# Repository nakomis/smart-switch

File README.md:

# Petro: a 10 A mains Wi-Fi smart switch

## Support

If you find this useful, please consider buying me a coffee:

## Table of Contents

<!-- toc -->

- [What it is](#what-it-is)
- [⚠️ Safety](#%E2%9A%A0%EF%B8%8F-safety)
- [Architecture Diagram](#architecture-diagram)
- [Repository Layout](#repository-layout)
- [Status](#status)
- [Architecture Diagrams](#architecture-diagrams)
- [Licence](#licence)
- [Support](#support)

<!-- tocstop -->

## What it is

Petro is a home-built Wi-Fi smart switch: an in-line cord unit (cable in, cable out) that switches a
resistive load of up to **10 A at 230 V AC**. It has:

- energy metering (voltage, current, power and energy totals), from a BL0939;
- one tactile button that cycles **on → off → auto**;
- a multi-colour status LED for the mode, boot, Wi-Fi, pairing and faults;
- control over MQTT through AWS IoT Core, using Martin's Fleet device service, with OTA
  updates and rollback;
- Alexa Smart Home control;
- back-up over-current and over-temperature trips in firmware.

It runs on an ESP32-C6, powered straight from the mains by a non-isolated buck converter, so the
whole board is at mains potential: it is only ever powered closed in its case, and USB is used
only with mains unplugged.

Petro is named after a Clone Wars youngling: microcontrollers in this house are Younglings.

## ⚠️ Safety

**This is a mains device, built for its author's own home. It is not a product, it will never be
sold or given away, and it has not been safety tested or UKCA marked.** The designs are published
for interest. If you build one, you do so at your own risk: mains electricity can kill, and a badly
built 10 A switch can start a fire.

## Architecture Diagram

The board's block diagram and the system diagram are still to come
(`docs/architecture/smart-switch.drawio`).

## Repository Layout

| Path | What's there |
|---|---|
| `pcb/` | The board, generated as code: a Python generator for KiCad 10, with DRC rules for mains creepage and 10 A tracks, and outputs for PCBWay and JLCPCB |
| `firmware/` | ESP-IDF 5.5 firmware for the ESP32-C6: portable C with host tests, plus the IDF project |
| `case/` | The enclosure: a printed case in UL94 V-0 flame-retardant filament, with glands and cord grips |
| `infra/` | AWS, as CDK in TypeScript: the units' IoT Things, CI's role, and the Alexa skill's Lambda, account linking and state |
| `alexa/` | The Alexa Smart Home skill as code: its manifest and icons (`docs/alexa-setup.md`) |
| `docs/` | Design notes, the test procedures for the safety gates, the Alexa setup, the logo |
| `.github/workflows/` | CI |

## Status

The board (PETRO-2) is designed and routed: revision B, 120 × 80 mm with 4 mm rounded corners, two layers, generated as code
in `pcb/` and DRC-clean against its own mains rules. It passed its design review (safety gate 1) and five
were ordered on 5 Nov 2026. The firmware (PETRO-3 to PETRO-5) and the case (PETRO-6) are next.
The safety gates' procedures and results are in [`docs/testing/`](docs/testing/README.md).
The design decisions, and why, are in [`docs/DESIGN.md`](docs/DESIGN.md).

## Architecture Diagrams

`docs/architecture/smart-switch.drawio` will be the source for the diagram above. The SVG is
auto-regenerated on commit by the pre-commit hook in `.githooks/pre-commit`.

To activate the hook after cloning:

```bash
git config core.hooksPath .githooks
```

## Licence

[CC0 1.0 Universal](LICENSE).

## Support

If you find this useful, please consider buying me a coffee:

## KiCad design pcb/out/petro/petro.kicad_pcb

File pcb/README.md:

# Board

The Petro board, generated as code (Python → KiCad 10) on the nakostat heatlink pipeline
(`nakostat/pcb/heatlink/`, itself from tinycrypt's), with DRC rules for mains creepage and a
`Mains16A` net class. Work item: PETRO-2, after the design decisions in PETRO-1.

The pipeline is copied, not shared: `board/` holds the generic modules, and Petro's own board
arrives as `board/petro_board.py` and `build.py`.

| Module | What it does |
|---|---|
| `board/sexpr.py` | Reads and writes KiCad s-expressions |
| `board/kicadlib.py` | Loads footprints (pads, courtyards) and symbol pin tables |
| `board/parts.py` | The parts catalogue: LCSC number, footprint, symbol, body extent, 3D model fixes, manufacturer |
| `board/netlist.py` | `Circuit` (parts and nets) and `check()` (single-pad nets, nets with several outputs, unconnected power pins) |
| `board/placement.py` | `Placement` and rotated bounding boxes |
| `board/kicad_pcb.py` | Writes `.kicad_pcb`, `.kicad_pro` (net classes) and `.kicad_dru` (mains rules) |
| `board/dsn.py`, `board/ses.py`, `board/route.py` | Specctra DSN out, Freerouting headless, SES back in |
| `board/cleanup.py` | After routing, drops vias that join only one layer and track stubs that lead nowhere |
| `board/fab.py` | BOMs (JLCPCB and PCBWay), CPL, gerbers, drill, renders, STEP |
| `board/art.py` | Turns a black-and-white PNG into a silkscreen portrait |
| `board/rules.py` | The mains rules: potential groups, fault scenarios, the working-voltage matrix, IEC 60664-1 creepage, the generated `.kicad_dru` and net classes, and the creepage check within barrier parts |

## Mains rules

Every mains net is in one potential group:

| Group | What's in it |
|---|---|
| LINE | Live before F1 |
| LIVE | Live after F1 |
| PSU | Live after F2: the supply's DC bus |
| SWNODE | The LNK306's switching node and what rides on it (SW, BP, FB, FBH) |
| NEUTRAL | Neutral, and every other net: GND is neutral |
| LOAD | The relay's output |
| DIV1–4 | The voltage divider's chain |

Rev B is non-isolated (`Rules(rest="NEUTRAL")`): every net not named in a group sits at neutral,
so the low-voltage side is one more mains potential. Each fault scenario (relay closed or open,
either fuse blown) gives every group a potential. The worst difference between two groups is
their working voltage, and IEC 60664-1 Table F.4 (pollution degree 2, material group III) turns
that into a creepage distance: 2.5 mm between the mains potentials, less down the divider's chain,
and 1.0 mm for SWNODE (`Rules.reduced`: functional insulation inside the converter). `rules.py`
writes the result as KiCad DRC rules, and `tests/test_rules.py` proves each rule fails a board
that breaks it.

`rules.py` still supports the isolated designs (rev A's 8 mm mains↔SELV barrier, and rev B's
isolated J3 as a SELV island, with `barrier_creepage()` for the pads of certified barrier parts),
but Petro's board uses neither now: see the tags in `docs/DESIGN.md`.

The high-current nets (N_IN, N_OUT, L_IN, L_F, L_OUT) are not tracks but solid pours on both
layers, stitched with vias (`petro_board.mains_zones()` and `stitch_vias()`). Each pour is drawn
as a generous polygon, and KiCad's fill trims it to the rules. Its `min_thickness` is the
IPC-2221 width for 8 A at 1 oz (3.5 mm), half the 16 A design current, so KiCad drops any neck
thinner than that. `tests/test_copper.py` refills the zones and checks that each layer, on its
own, is one piece reaching every through-hole pad of its net, so the two layers carry the current
in parallel. The GND pour covers the low-voltage area, kept 2.5 mm from every other potential.

## Routing

`build.py --route` routes in one Freerouting pass: the low-voltage nets inside the low-voltage
area (`petro_board.lv_area()`), with keep-outs round everything at another potential, since the
router knows only plain clearances. By hand, before routing (`petro_board.hand_wiring()`): the
divider chain, the supply's high-voltage nets, the shunt's Kelvin pair (into R10), the LDO's
ground and the USB protection's flow-through ties. DRC then runs with the generated rules, and
the build fails on any error, unconnected item or broken mains pour.

## Setting up

```bash
cd pcb
ASDF_PYTHON_VERSION=3.11.15 python3 -m venv .venv
.venv/bin/pip install -r requirements.txt
cp ~/repos/nakomis/nakostat/pcb/heatlink/freerouting/freerouting-2.5.0.jar freerouting/   # 64 MB, not committed
```

Java comes from asdf. KiCad 10 must be installed at `/Applications/KiCad/`.

- `./fetch_parts.sh` fetches any missing footprints and symbols from EasyEDA. It skips parts it
  already has, and waits 20 s between parts because EasyEDA rate-limits.
- `./fetch_models.sh` fetches the 3D models, which aren't committed.

## Tests

```bash
TEST_MAX_WORKERS=2 .venv/bin/python -m pytest -q tests
```

Tests marked `kicad` run `kicad-cli` (DRC, position files) or read KiCad's footprint library.
Without KiCad they're skipped, not failed, and the rest still run: that's how CI runs them (PETRO-9),
so the DRC-backed tests still need a run on the Mac before a board is ordered. `KICAD_CLI` and
`KICAD_FP` override the macOS paths.

The generic tests run on a small fixture board (`tests/fixture_board.py`), not on Petro's board.
The routing test routes that fixture with Freerouting **in a temporary directory**. Freerouting
isn't deterministic, so a test that routed in place would overwrite `out/` (the heatlink nearly
committed a re-routed board after its order had been quoted). The board that gets ordered is
committed and tagged.

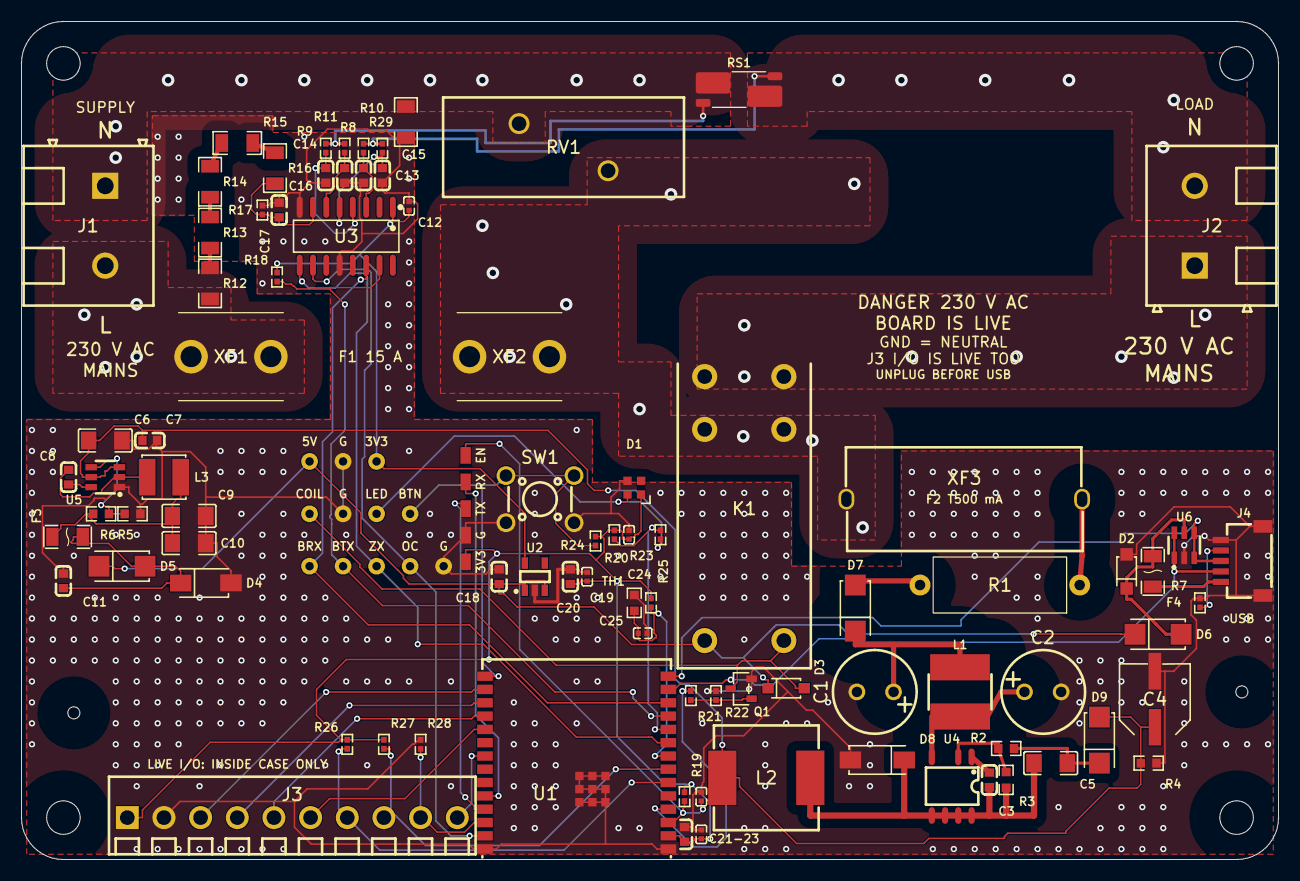
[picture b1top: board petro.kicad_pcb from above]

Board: 2 copper layers, 120.0 x 80.0 mm, 106 parts (0 on the bottom side), 60 nets.

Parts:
C1, C2: 4.7uF 400V; CAP-TH_BD8.0-P3.50-D0.6-FD
C3, C7, C8: 100nF; C0603
C4: 220uF 25V; CAP-SMD_BD6.3-L6.6-W6.6-LS7.2-FD
C5, C6: 10uF 50V; C1206
C9, C10: 22uF 25V; C1206
C11, C18, C19, C21: 10uF; C0603
C12, C20, C22, C24, C25: 100nF; C0402
C13, C14, C15, C16, C17: 33nF; C0603
C23: 1uF; C0402
D1: SK6812-EC20; LED-SMD_4P-L2.0-W2.0-BR
D2: SMF5.0A; SOD-123FL_L2.7-W1.8-LS3.8-RD
D3: 1N4148W; SOD-123F_L2.7-W1.6-LS3.8-RD
D4: SMAJ5.0A; SMA_L4.3-W2.6-LS5.0-RD
D5, D6: SS34; SMA_L4.3-W2.6-LS5.2-RD
D7, D9: M7; SMA_L4.3-W2.6-LS5.2-RD
D8: US1M; SMA_L4.4-W2.8-LS5.4-RD
F3: 1.1A PTC; F1206
F4: 500mA PTC; F1206
H1, H2, H3, H4: M3 hole, unplated; MountingHole_M3_3.2mm_NPTH
H5, H6: tooling hole; ToolingHole_1.152mm_NPTH
J1, J2: DG636-7.62-02P; CONN-TH_DG636-7.62-02P-14-02A-H
J3: DB125-3.5-10P-GN-S; CONN-TH_10P-P3.50_DIBO_DB125-3.5-10P-GN-S
J4: SM05B-SRSS-G-TB; CONN-SMD_SM05B-SRSS-G-TB-LF-SN
K1: HF115F-I/005-1HS3A; RELAY-TH_HF115F-XXX-1HS3
L1: 1mH 350mA; IND-SMD_L6.0-W6.0_FNR60XXS
L2: 680uH 1A; IND-SMD_L10.0-W10.0_ABG10A50M4R7
L3: 3.3uH; IND-SMD_L4.0-W4.0
Q1: AO3400A; SOT-23-3_L2.9-W1.3-P1.90-LS2.4-BR
R1: 10R 2W fusible; R_Axial_FKN2WS_P15.24mm
R2: 13k; R0603
R3: 2k; R0603
R4: 3k3; R0603
R5: 56k; R0603
R6: 10k; R0603
R7: 5k1; R0402
R8, R9, R10, R11: 1k; R0402
R12, R13, R14, R15, R16: 390k; R1206
R17: 470R; R0402
R18, R19, R20, R24, R25: 10k; R0402
R21: 100R; R0402
R22, R28: 100k; R0402
R23: 330R; R0402
R26, R27: 4k7; R0402
R29: 0R; R1206
RS1: 1mR; R_Shunt_Vishay_WSK2512_6332Metric_T2.21mm
RV1: TMOV20RP275E; RES-TH_L23.0-W9.5-P8.50-D0.9-S4.50
SW1: TS-1002 7mm; SW-TH_4P-L6.0-W6.0-P4.50-LS6.5_TS-1002-07026
TH1: 10k NTC; R0603
TP1: Debug pads; DebugPads_1x5_P2.54
TP2, TP3, TP4, TP5, TP6, TP7, TP8, TP9, TP10, TP11, TP12, TP13: test hole; TestHole_0.8mm
U1: ESP32-C6-WROOM-1-N8; ESP32-C6-WROOM-1_NoThermalVias
U2: AP2112K-3.3TRG1; SOT-25-5_L2.9-W1.6-P0.95-LS2.8-BL
U3: BL0939; SOP-16_L9.9-W3.9-P1.27-LS6.0-BL
U4: LNK306DN; SOIC-8_7P-L4.9-W3.9-P1.27-LS6.0-BL-PE3
U5: TPS563201; SOT-23-6_L2.9-W1.6-P0.95-LS2.8-BR
U6: SRV05-4; SOT-23-6_L2.9-W1.6-P0.95-LS2.8-BL-1
XF1, XF2: 6.35mm fuse clip 30A; FuseClip_Littelfuse_0122_6.35mm
XF3: 5x20 holder; FUSE-TH_65600001009

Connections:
+3V3: C12.1, C19.1, C20.1, C21.1, C22.1, C24.1, D1.1, J3.1, R18.2, R19.2, R20.2, R24.2, R25.2, R26.2, R27.2, TP1.5, TP9.1, U1.2, U2.5, U3.1
+5V: C18.1, D3.1, D5.1, D6.1, K1.1, TP7.1, U2.1, U2.3
+12V: C4.1, C6.1, C7.1, D9.2, L2.2, R4.1, U5.3, U5.5
BL_RX: TP2.1, U1.12, U3.14
BL_TX: R18.1, TP3.1, U1.11, U3.15
BP: C3.1, U4.1
BST5: C8.1, U5.6
BUTTON: R20.1, SW1.1, SW1.2, TP13.1, U1.15
CC: J4.4, R7.1
COIL: D3.2, K1.2, Q1.3, TP10.1
DIV1: R15.2, R16.1
DIV2: R14.2, R15.1
DIV3: R13.2, R14.1
DIV4: R12.2, R13.1
EN: C23.1, R19.1, TP1.1, U1.3
FB: R2.2, R3.1, U4.2
FB5: R5.2, R6.1, U5.4
FBH: C5.1, D9.1, R2.1
GND: C1.2, C2.2, C4.2, C6.2, C7.2, C9.2, C10.2, C11.2, C12.2, C13.2, C14.2, C15.2, C16.2, C17.2, C18.2, C19.2, C20.2, C21.2, C22.2, C23.2, C24.2, C25.2, D1.3, D2.2, D4.2, D8.2, J3.2, J4.5, J4.6, J4.7, Q1.2, R4.2, R6.2, R7.2, R17.2, R22.2, R28.2, R29.1, SW1.3, SW1.4, TH1.2, TP1.4, TP6.1, TP8.1, TP11.1, U1.1, U1.28, U1.29, U1.30, U1.31, U1.32, U1.33, U1.34, U1.35, U1.36, U1.37, U2.2, U3.8, U3.12, U5.1, U6.2
I2C_SCL: J3.8, R27.1, U1.7
I2C_SDA: J3.7, R26.1, U1.6
IAN: C14.1, R9.2, U3.4
IAP: C13.1, R8.2, U3.3
IBN: C16.1, R11.2, U3.6
IBP: C15.1, R10.2, U3.5
IO_IN: J3.9, R28.1, U1.26
IO_OUT: J3.10, U1.21
KGND: R9.1, R11.1, RS1.2
LED: R23.2, R24.1, U1.10
LED_DIN: D1.4, R23.1, TP12.1
L_F: K1.5, K1.6, RV1.1, XF2.1, XF3.1
L_IN: J1.2, R12.1, XF1.1
L_OUT: J2.1, K1.7, K1.8
L_PSU: R1.1, XF3.2
L_RF: D7.2, R1.2
NTC: C25.1, R25.1, TH1.1, U1.8
N_IN: J1.1, R29.2, RS1.1, RV1.2
N_OUT: J2.2, RS1.4
OC: TP5.1, U1.27, U3.10
RELAY: R21.2, U1.4
RELAY_G: Q1.1, R21.1, R22.1
SENSE: R8.1, R10.1, RS1.3
SPI_CS: J3.6, U1.19
SPI_MISO: J3.5, U1.18
SPI_MOSI: J3.4, U1.17
SPI_SCLK: J3.3, U1.16
SW: C3.2, C5.2, D8.1, L2.1, R3.2, U4.5, U4.6, U4.7, U4.8
SW5: C8.2, L3.1, U5.2
UART_RX: TP1.2, U1.24
UART_TX: TP1.3, U1.25
USB_DM: J4.2, U1.13, U6.1, U6.6
USB_DP: J4.3, U1.14, U6.3, U6.4
VBULK: C2.1, L1.2, U4.4
VBULK1: C1.1, D7.1, L1.1
VBUS: D2.1, D6.2, F4.2, U6.5
VBUS_IN: F4.1, J4.1
VP: C17.1, R16.2, R17.1, U3.7
VPSU: C9.1, C10.1, F3.1, L3.2, R5.1
VPSU_F: C11.1, D4.1, D5.2, F3.2
ZX: TP4.1, U1.9, U3.9

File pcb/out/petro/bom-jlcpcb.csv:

Comment,Designator,Footprint,LCSC Part #
4.7uF 400V,"C1,C2",CAP-TH_BD8.0-P3.50-D0.6-FD,C112482
100nF,"C3,C7,C8",C0603,C14663
220uF 25V,C4,CAP-SMD_BD6.3-L6.6-W6.6-LS7.2-FD,C4747974
10uF 50V,"C5,C6",C1206,C13585
22uF 25V,"C9,C10",C1206,C12891
10uF,"C11,C18,C19,C21",C0603,C19702
100nF,"C12,C20,C22,C24,C25",C0402,C1525
33nF,"C13,C14,C15,C16,C17",C0603,C21117
1uF,C23,C0402,C52923
SK6812-EC20,D1,LED-SMD_4P-L2.0-W2.0-BR,C2909058
SMF5.0A,D2,SOD-123FL_L2.7-W1.8-LS3.8-RD,C19077497
1N4148W,D3,SOD-123F_L2.7-W1.6-LS3.8-RD,C81598
SMAJ5.0A,D4,SMA_L4.3-W2.6-LS5.0-RD,C2925443
SS34,"D5,D6",SMA_L4.3-W2.6-LS5.2-RD,C8678
M7,"D7,D9",SMA_L4.3-W2.6-LS5.2-RD,C95872
US1M,D8,SMA_L4.4-W2.8-LS5.4-RD,C412437
1.1A PTC,F3,F1206,C126818
500mA PTC,F4,F1206,C163512
DB125-3.5-10P-GN-S,J3,CONN-TH_10P-P3.50_DIBO_DB125-3.5-10P-GN-S,C5184956
SM05B-SRSS-G-TB,J4,CONN-SMD_SM05B-SRSS-G-TB-LF-SN,C265419
1mH 350mA,L1,IND-SMD_L6.0-W6.0_FNR60XXS,C168102
680uH 1A,L2,IND-SMD_L10.0-W10.0_ABG10A50M4R7,C48934988
3.3uH,L3,IND-SMD_L4.0-W4.0,C602030
AO3400A,Q1,SOT-23-3_L2.9-W1.3-P1.90-LS2.4-BR,C20917
13k,R2,R0603,C22797
2k,R3,R0603,C22975
3k3,R4,R0603,C22978
56k,R5,R0603,C23206
10k,R6,R0603,C25804
5k1,R7,R0402,C25905
1k,"R8,R9,R10,R11",R0402,C11702
390k,"R12,R13,R14,R15,R16",R1206,C17933
470R,R17,R0402,C25117
10k,"R18,R19,R20,R24,R25",R0402,C25744
100R,R21,R0402,C25076
100k,"R22,R28",R0402,C25741
330R,R23,R0402,C25104
4k7,"R26,R27",R0402,C25900
0R,R29,R1206,C17888
1mR,RS1,R_Shunt_Vishay_WSK2512_6332Metric_T2.21mm,C4248455
TS-1002 7mm,SW1,SW-TH_4P-L6.0-W6.0-P4.50-LS6.5_TS-1002-07026,C455095
10k NTC,TH1,R0603,C2892547
ESP32-C6-WROOM-1-N8,U1,ESP32-C6-WROOM-1_NoThermalVias,C5366877
AP2112K-3.3TRG1,U2,SOT-25-5_L2.9-W1.6-P0.95-LS2.8-BL,C51118
BL0939,U3,SOP-16_L9.9-W3.9-P1.27-LS6.0-BL,C2836697
LNK306DN,U4,SOIC-8_7P-L4.9-W3.9-P1.27-LS6.0-BL-PE3,C34318
TPS563201,U5,SOT-23-6_L2.9-W1.6-P0.95-LS2.8-BR,C116592
SRV05-4,U6,SOT-23-6_L2.9-W1.6-P0.95-LS2.8-BL-1,C7420376

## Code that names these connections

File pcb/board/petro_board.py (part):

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# sensors and the PIR can wake the chip with the main core asleep; SPI on 18-21. IN (3), OUT (23)
# and SPI are on the module's left-hand column, J3's side; LP_I2C has no other pins. GPIO22 and
# GPIO15 are spare.
GPIO = {"BUTTON": 9, "LED": 8, "USB_DM": 12, "USB_DP": 13, "UART_TX": 16, "UART_RX": 17,
        "NTC": 0,           # board temperature, ADC1_CH0
        "ZX": 1,            # BL0939 zero cross
        "OC": 2,            # BL0939 I_leak (channel B fast over-current)
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# --- connectors ----------------------------------------------------------------------------------
# J1 / J2: line in and load out (Degson DG636, 7.62 mm). Earth does not touch the board. Both
# turned so their wire openings face their end of the board (J1 left, J2 right), neutral on top.
J1_PINS = {"1": "N_IN", "2": "L_IN"}           # rotated 270: pad 1 on top
J2_PINS = {"1": "L_OUT", "2": "N_OUT"}         # rotated 90: pad 2 on top
# J4: the house USB connector (tinycrypt's J1, as on the heatlink): 1 VBUS, 2 D-, 3 D+, 4 CC,
# 5 GND; pads 6/7 are the shell tabs. Inside the case: reachable only with the case off.
USB_PINS = {"1": "VBUS_IN", "2": "USB_DM", "3": "USB_DP", "4": "CC", "5": "GND"}
DEBUG_PINS = {"1": "EN", "2": "UART_RX", "3": "UART_TX", "4": "GND", "5": "+3V3"}
# J3: the I/O terminal (10-way, 3.5 mm) for parts inside the case, straight from the ESP32: 3.3 V
# and ground, SPI, I2C, one input (a PIR, an interrupt) and one output. At mains potential, like
# the rest of the board. J4 (the heatlink's IDC header) is gone: the C6 has no pins left for it.
IO_PINS = {"1": "+3V3", "2": "GND", "3": "SPI_SCLK", "4": "SPI_MOSI", "5": "SPI_MISO",
           "6": "SPI_CS", "7": "I2C_SDA", "8": "I2C_SCL", "9": "IO_IN", "10": "IO_OUT"}

# --- the mains rules (non-isolated mode: every other net sits at neutral) --------------------------
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    # ---- the supply: F2, then PI's LNK306 high-side buck (12 V) ----------------------------------
    two("FUSEHOLD", "XF3", "L_F", "L_PSU")                      # F2, T500 mA
    two("RFUSE", None, "L_PSU", "L_RF")                         # fusible, flameproof: inrush and fault
    pins("RECT", "D7", A="L_RF", K="VBULK1")                          # half-wave, in the live leg
    pins("C4U7HV", _plus="VBULK1", _minus=gnd)                  # pi filter: C4, L2, C5
    two("L1MF", None, "VBULK1", "VBULK")
    pins("C4U7HV", _plus="VBULK", _minus=gnd)
    u4 = part("LNK306", "U4")
    c.connect("VBULK", (u4, "D"))
    c.connect("SW", (u4, "S"))
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    two("L680U", None, "SW", v12)                               # output inductor, 680 uH (>= 0.5 mH, PI MDCM)
    pins("FASTREC", "D8", A=gnd, K="SW")                              # freewheel (US1M, 75 ns)
    pins("C220U", _plus=v12, _minus=gnd)
    pins("RECT", "D9", A=v12, K="FBH")                                # feedback: samples the output...
    two("C10U50", None, "FBH", "SW")                            # ...onto C3, across SOURCE
    two("R13K", None, "FBH", "FB")                              # 1.65 V at FB: 12.4 V out
    two("R2K", None, "FB", "SW")
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    c.connect("RELAY_G", (q1, "G"))
    two("R100", None, "RELAY_G", "RELAY")
    two("R100K", None, "RELAY_G", gnd)
    c.connect("RELAY", (u1, modpin(GPIO["RELAY"])))

    # LED: SK6812-EC20 on 3V3 with 100 nF, data through 330R.
    d1 = part("LED", "D1")
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    two("R10K", None, "LED", v33)                               # GPIO8 strap: high at reset
    two("C100N", None, v33, gnd)

    # NTC: 10k NTC to GND under 10k to 3V3 on GPIO0 (about 1.65 V at 25 C), 100 nF across.
    c.connect("NTC", (u1, modpin(GPIO["NTC"])))
    two("NTC", "TH1", "NTC", gnd)
    two("R10K", None, "NTC", v33)
    two("C100N", None, "NTC", gnd)
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    "TP1": (42.4, 46.5, 0),
    "SW1": (49.5, 45.6, 0), "R20": (54.8, 49.6, 90),
    "D1": (58.5, 44.5, 0), "C24": (58.0, 49.0, 90), "R23": (61.0, 49.0, 90), "R24": (56.6, 49.0, 90),
    # relay driver (between the relay's coil pins and the module) and the NTC beside it
    "R21": (63.9, 64.35, 90), "R22": (66.3, 64.35, 90), "Q1": (68.7, 63.7, 0), "D3": (73.0, 63.65, 0),
    # the NTC beside the relay's left-hand side, above the module
    "TH1": (58.5, 55.5, 90), "R25": (60.1, 55.5, 90), "C25": (59.3, 58.4, 0),
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             (45, 8.6), (12, 8.6), (12, 19), (3, 19)],
    "N_OUT": [(69.3, 3), (117, 3), (117, 19), (106, 19), (106, 8.6), (75, 8.6), (75, 10), (69.3, 10)],
    "L_IN": [(3, 21), (14, 21), (14, 25.4), (20, 25.4), (20, 28.5), (27, 28.5), (27, 35.5), (3, 35.5)],
    # live after F1: one band under the relay's L_F pins (y 37.6-41.5, 2.5 mm below L_OUT and
    # above the low-voltage area) joining the main block, the MOV's arm and XF3's column; each
    # arm and corner at least MAINS_MIN_WIDTH across so the fill stays one piece
    "L_F": [(40, 17.5), (54, 17.5), (54, 13), (81, 13), (81, 19.5), (57, 19.5), (57, 32.5), (62, 32.5),
            (62, 37.6), (81.5, 37.6), (81.5, 49.5), (76, 49.5), (76, 41.5), (57, 41.5), (57, 35.5),
            (40, 35.5)],
    # load: its bottom edge on the relay's L_OUT pins' lower edge (y 35.1), its left edge just past
    # them, so the L_F band and column fit beneath and beside it
    "L_OUT": [(64.5, 26), (104, 26), (104, 20.5), (117, 20.5), (117, 35.1), (64.5, 35.1)],
}
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# No reference designators (they ran together and mostly sat under parts; the component key PDF
# names them). Labels only where a person needs them, each where there is room: the front for
# what is used from the front, the back for the rest.
TEST_LABELS = {"BL_RX": "BRX", "BL_TX": "BTX", "ZX": "ZX", "OC": "OC", "GND": "G", "+5V": "5V",
               "+3V3": "3V3", "COIL": "COIL", "LED_DIN": "LED", "BUTTON": "BTN"}
DEBUG_LABELS = {"1": "EN", "2": "RX", "3": "TX", "4": "G", "5": "3V3"}
IO_LABELS = {"1": "3V3", "2": "G", "3": "SCK", "4": "MOSI", "5": "MISO", "6": "CS", "7": "SDA",
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             "/* Petro rev B: ESP32-C6-WROOM-1-N8 (idf.py set-target esp32c6). */",
             "/* Debug pads TP1, from the top: " + ", ".join(DEBUG_LABELS.values()) + ".",
             "   EN is the chip enable (bridge it to G to reset); RX/TX are UART0. */",
             "/* The relay is active-high (low-side FET); the button is active-low (GPIO9, also the",
             "   boot strap); the LED is on GPIO8 (a strap: pulled up). BL_TX/BL_RX are UART1 to the",
             "   BL0939; ZX is its zero cross, OC its fast over-current. */",
             "/* Rev B is NON-ISOLATED: GND is tied to neutral, so every pin and pad is at mains",
             "   potential whenever the unit is plugged in, J3 included. Bench work",
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
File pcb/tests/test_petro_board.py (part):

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def test_j3_carries_the_board_rails_spi_i2c_in_and_out():
    assert C.instances["J3"].part.key == "IO10"
    assert {pad: net("J3", pad) for pad in pb.IO_PINS} == pb.IO_PINS
    assert list(pb.IO_PINS.values()) == ["+3V3", "GND", "SPI_SCLK", "SPI_MOSI", "SPI_MISO",
                                         "SPI_CS", "I2C_SDA", "I2C_SCL", "IO_IN", "IO_OUT"]


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def test_i2c_is_pulled_up_and_in_pulled_down():
    for sig in ("I2C_SDA", "I2C_SCL"):
        assert len([r for r in by_key("R4K7") if nets_of(r) == {sig, "+3V3"}]) == 1, sig
    assert len([r for r in by_key("R100K") if nets_of(r) == {"IO_IN", "GND"}]) == 1


def test_the_mains_parts_are_hand_fit():
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    assert net(u, "SW") == "SW5" and net(u, "VFB") == "FB5"
    assert nets_of(by_key("L3U3")[0]) == {"SW5", "VPSU"}
    boot = [r for r in by_key("C100N6") if nets_of(r) == {"SW5", "BST5"}]
    assert net(u, "VBST") == "BST5" and len(boot) == 1
    top, bottom = by_key("R56K")[0], by_key("R10K6")[0]
    assert nets_of(top) == {"VPSU", "FB5"} and nets_of(bottom) == {"FB5", "GND"}
    assert 4.9 < 0.768 * (1 + 56 / 10.0) < 5.1       # 5.07 V
    assert len([r for r in by_key("C22U") if nets_of(r) == {"VPSU", "GND"}]) == 2


def test_diode_or_feeds_5v_from_the_supply_or_usb():
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
def test_bl0939_is_wired_straight_to_the_esp32():
    assert net("U3", "VDD") == "+3V3" and net("U3", "GND") == net("U3", "SEL") == "GND"
    for pin, k in (("TX/SDO", "BL_TX"), ("RX/SDI", "BL_RX"), ("ZX", "ZX"), ("I_leak", "OC")):
        assert net("U3", pin) == k and net("U1", pb.modpin(pb.GPIO[k])) == k
    assert len([r for r in by_key("R10K") if nets_of(r) == {"BL_TX", "+3V3"}]) == 1


# --- the low-voltage side ---------------------------------------------------------------------------
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    assert {net("K1", "COIL1"), net("K1", "COIL2")} == {"+5V", "COIL"}
    assert net("Q1", "D") == "COIL" and net("Q1", "S") == "GND" and net("Q1", "G") == "RELAY_G"
    assert (net("D3", "K"), net("D3", "A")) == ("+5V", "COIL")
    assert net("U1", pb.modpin(pb.GPIO["RELAY"])) == "RELAY"


def test_led_is_the_sk6812():
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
